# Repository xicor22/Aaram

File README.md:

# Aaram  
PCB design for retro fitting old switch boards with new tech to control it remotely using ESP32-C6-Mini-N1.

## Features
1. Controls 4 loads using
  - 1 Triac 
      > Note: Triac circuit has added protection for the back EMF generated by inductive load like fan.
  - 3 Relays for controlling other resistive loads
      > Try not use heavy inductive load using relays. During testing, the MCU was bugging out when load was switched.
2. Input from switches.
      - To reduce rewiring the whole switch board, directly connect the rocker switch output terminal to the input provided on the board.
      - The FULL BRIDGE RECTIFIER rectifies the AC which is sent to the quad channel opto with a 100k resistor in series for current limiting. The output from the opto is read by the ESP.
3. Fuse holder in series with the AC input for overload protection. 
4. Varistor on all AC output terminals for protection from transient spikes.
5. Added support for IR receiver and transmitter.
6. Uses DHT22 for temperature and humidity sensor.
7. ESPHome Yaml config - [Link](https://github.com/xicor22/Aaram/blob/main/ESPHome_Template.yaml)
## Schematic

## Images
|View|Image|
|----|-----|
|Both Layers| |
|1<sup>st</sup> Layer| |
|2<sup>nd</sup> Layer| |
|3D Top view| |
|3D Bottom view| |

## To-Do
1. ~~Design 3D printables case for the PCB.~~ **Done**
2. Update ESPHOME yaml config.

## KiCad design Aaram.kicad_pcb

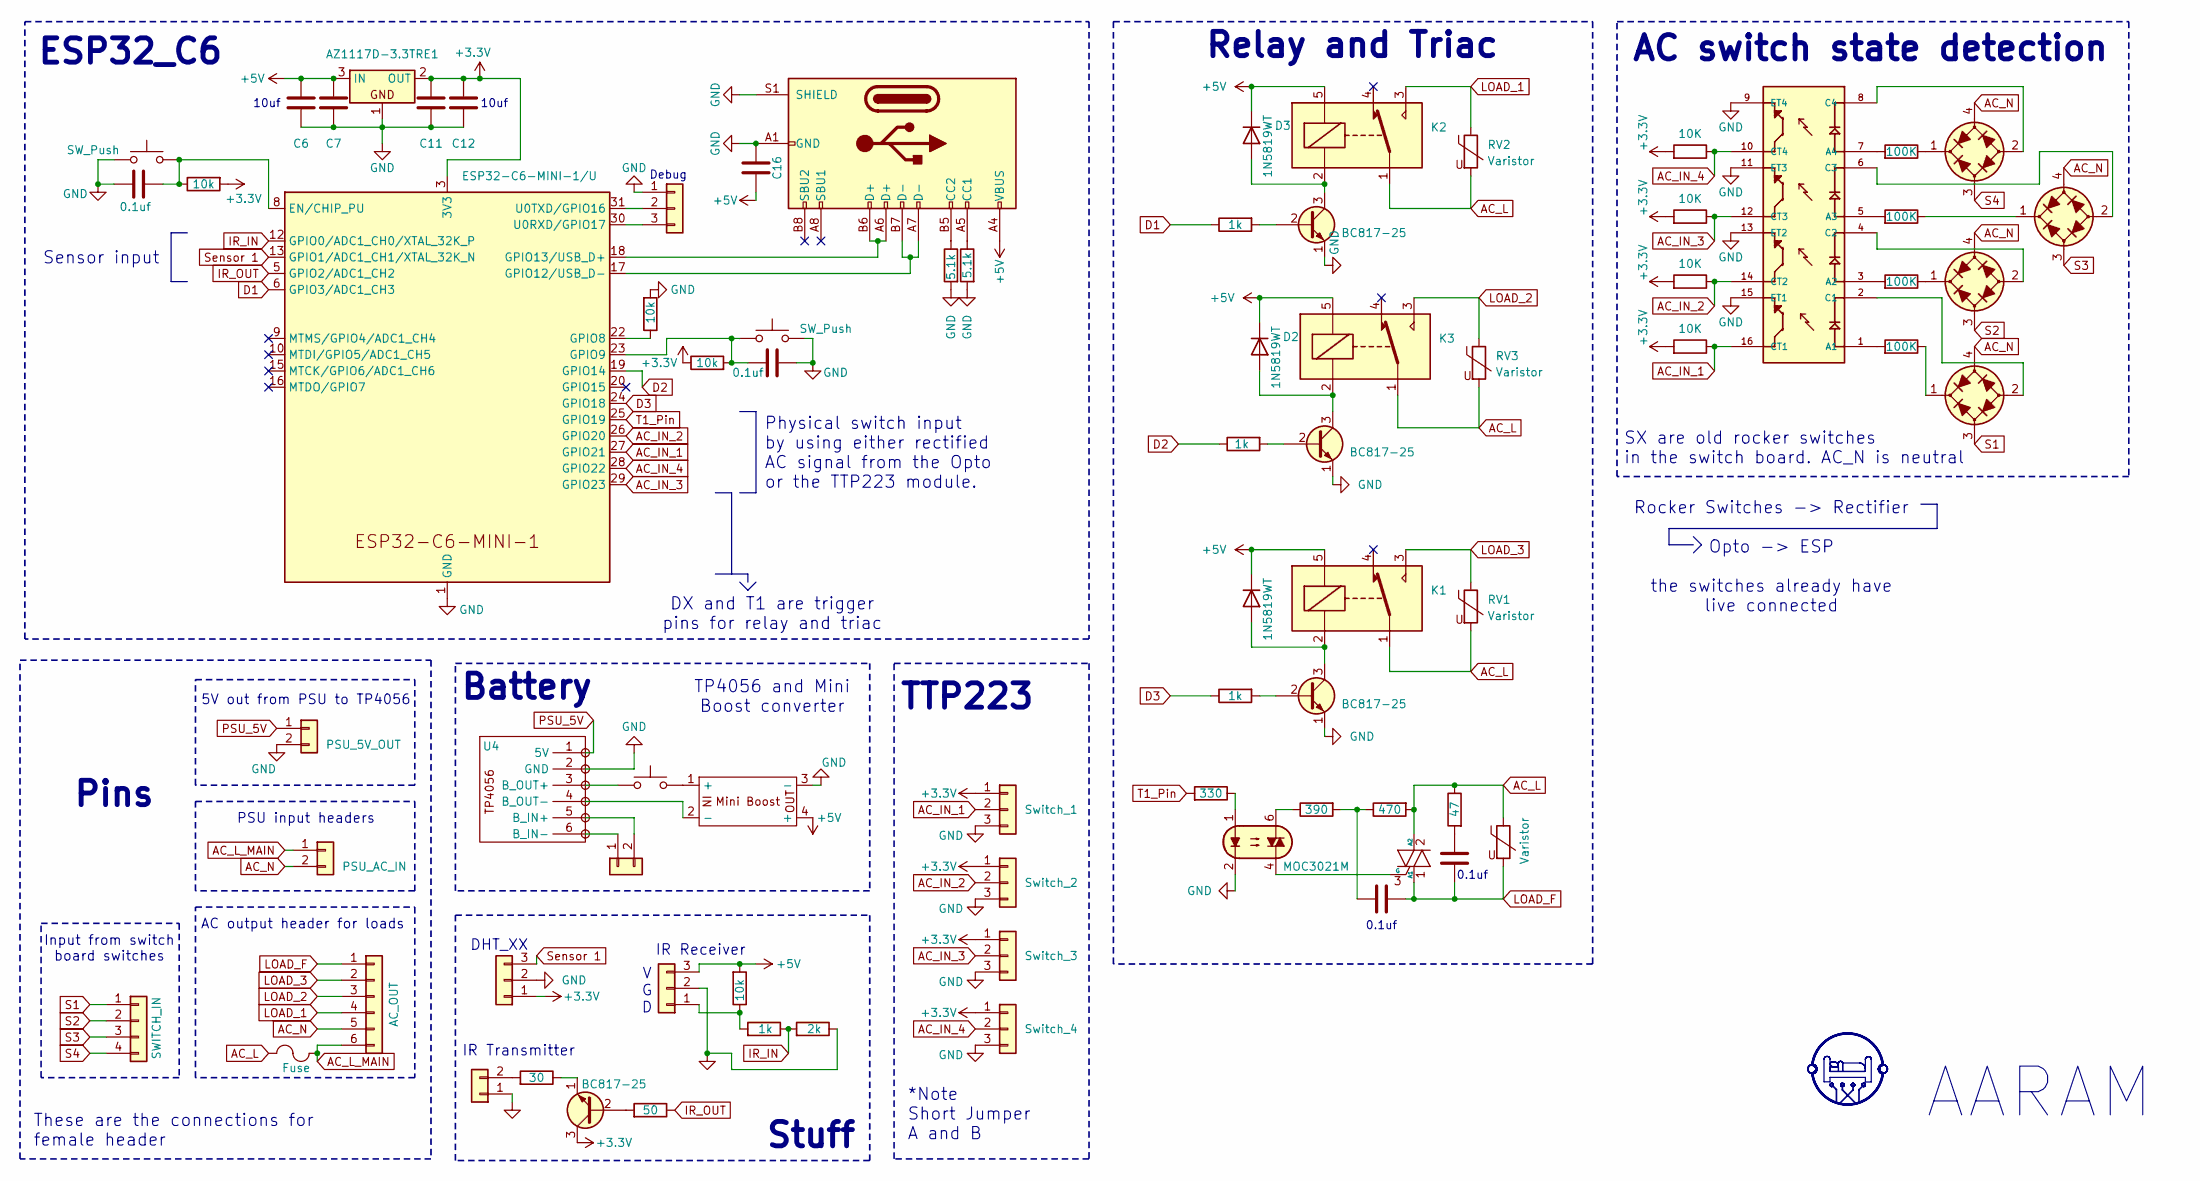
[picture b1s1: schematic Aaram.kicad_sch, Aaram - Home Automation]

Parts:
C1, C4: CP_Axial_L10.0mm_D4.5mm_P15.00mm; Axial_Capacitor_P10mm_W4.5mm
C6, C7, C11, C12: 10uf; C_1206_3216Metric_Pad1.42x1.75mm
C16: 1uf; C_1206_3216Metric_Pad1.42x1.75mm
C18, C19: 0.1uf; C_1206_3216Metric_Pad1.42x1.75mm
D1, D2, D3: 1N5819WT; D_SMA_Handsoldering
D8, D9, D10, D11: MB6S; Diode_Bridge_MBS
F1: Fuse; BLX-A
J1, J10, J11: Conn_01x03; PinSocket_1x03_P2.54mm_Vertical
J2, J9: Conn_01x02; PinSocket_1x02_P2.54mm_Vertical
J3: AC_OUT; 1x06_P5.00mm_D1.50mm
J4: SWITCH_IN; PinSocket_1x04_P2.54mm_Vertical
J5: PSU_5V_OUT; PinSocket_1x02_P2.54mm_Vertical
J6: PSU_AC_IN; PinSocket_1x02_P2.54mm_Vertical
J8: USB_C_Receptacle_USB2.0_16P; USB_C_Receptacle_GCT_USB4105-xx-A_16P_TopMnt_Horizontal
K1, K2, K3: 10A cube relay; Relay_SPDT_SANYOU_SRD_Series_Form_C
OC1: MOC3021M; DIP-6_W7.62mm_LongPads
Q1: BT136-600; TO-220-3_Vertical
Q2, Q3, Q4, Q5: BC817-25; TSOT-23_HandSoldering
R1, R2, R3, R9: 1k; R_1206_3216Metric_Pad1.42x1.75mm_HandSolder
R4: 330; R_1206_3216Metric_Pad1.42x1.75mm_HandSolder
R5: 47; R_2512_6332Metric_Pad1.52x3.35mm_HandSolder
R6: 390; R_2512_6332Metric_Pad1.52x3.35mm_HandSolder
R7: 470; R_2512_6332Metric_Pad1.52x3.35mm_HandSolder
R8: 2k; R_1206_3216Metric_Pad1.42x1.75mm_HandSolder
R10, R16, R21, R22: 10k; R_1206_3216Metric_Pad1.42x1.75mm_HandSolder
R11: 30; R_1206_3216Metric_Pad1.42x1.75mm_HandSolder
R12, R14: 5.1k; R_1206_3216Metric_Pad1.42x1.75mm_HandSolder
R13: 50; R_1206_3216Metric_Pad1.42x1.75mm_HandSolder
R15, R17, R19, R23: 100K; R_2512_6332Metric_Pad1.52x3.35mm_HandSolder
R20, R25, R26, R27: 10K; R_1206_3216Metric_Pad1.42x1.75mm_HandSolder
RV1, RV2, RV3, RV4: Varistor; Varistor_10D431K
SW1, SW4: SW_Push; Tactile switch 6x3
SW2: SW_Push; SMD Tactile switch
Switch_1, Switch_2, Switch_3, Switch_4: Conn_01x03_Socket; JST_SH_BM03B-SRSS-TB_1x03-1MP_P1.00mm_Vertical
U1: ESP32-C6-MINI-1/U; ESP32-C6-MINI-1
U2: AZ1117D-3.3TRE1; TO-252-2
U3: Mini_Boost
U4: TP4056-18650
U5: TLP281-4GB_F_; SOP127P780X200-16N

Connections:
+3.3V: C11.2, C12.2, J1.1, Q5.3 (C), R10.1, R20.1, R21.2, R25.1, R26.1, R27.1, Switch_1.1, Switch_2.1, Switch_3.1, Switch_4.1, U1.3 (3V3), U2.2 (OUT)
+5V: C6.2, C7.2, C16.1, D1.1 (K), D2.1 (K), D3.1 (K), J8.A4 (VBUS), J8.A9 (VBUS), J8.B4 (VBUS), J8.B9 (VBUS), J10.3, K1.5, K2.5, K3.5, R16.1, U2.3 (IN), U3.4 (+)
AC_IN_1: R26.2, Switch_1.2, U1.27 (GPIO21), U5.16 (CT1)
AC_IN_2: R25.2, Switch_2.2, U1.26 (GPIO20), U5.14 (CT2)
AC_IN_3: R20.2, Switch_3.2, U1.29 (GPIO23), U5.12 (CT3)
AC_IN_4: R27.2, Switch_4.2, U1.28 (GPIO22), U5.10 (CT4)
AC_L: F1.1, K1.1, K2.1, K3.1, Q1.2 (A2), R5.2, R7.1, RV1.2, RV2.2, RV3.2, RV4.1
AC_L_MAIN: F1.2, J3.6, J6.1
AC_N: D8.4 (2), D9.4 (2), D10.4 (2), D11.4 (2), J3.5, J6.2
D1: R2.2, U1.6 (GPIO3/ADC1_CH3)
D2: R1.2, U1.19 (GPIO14)
D3: R3.2, U1.24 (GPIO18)
GND: C6.1, C7.1, C11.1, C12.1, C16.2, C18.1, C19.1, J1.2, J2.1, J5.2, J8.A1 (GND), J8.A12 (GND), J8.B1 (GND), J8.B12 (GND), J8.S1 (SHIELD), J10.2, J11.1, OC1.2, Q2.1 (E), Q3.1 (E), Q4.1 (E), R8.2, R12.1, R14.1, R22.1, SW1.1, SW4.1, Switch_1.3, Switch_2.3, Switch_3.3, Switch_4.3, U1.1 (GND), U1.2 (GND), U1.11 (GND), U1.14 (GND), U1.36 (GND), U1.37 (GND), U1.38 (GND), U1.39 (GND), U1.40 (GND), U1.41 (GND), U1.42 (GND), U1.43 (GND), U1.44 (GND), U1.45 (GND), U1.46 (GND), U1.47 (GND), U1.48 (GND), U1.49 (GND), U1.50 (GND), U1.51 (GND), U1.52 (GND), U1.53 (GND), U2.1, U3.3 (-), U4.2 (GND), U5.9 (ET4), U5.11 (ET3), U5.13 (ET2), U5.15 (ET1)
IR_IN: R8.1, R9.2, U1.12 (GPIO0/ADC1_CH0/XTAL_32K_P)
IR_OUT: R13.2, U1.5 (GPIO2/ADC1_CH2)
LOAD_1: J3.4, K2.3, RV2.1
LOAD_2: J3.3, K3.3, RV3.1
LOAD_3: J3.2, K1.3, RV1.1
LOAD_F: C1.2, C4.2, J3.1, Q1.1 (A1), RV4.2
unnamed: C1.1, R6.1, R7.2
unnamed: C4.1, R5.1
unnamed: D1.2 (A), K1.2, Q4.3 (C)
unnamed: D2.2 (A), K3.2, Q2.3 (C)
unnamed: D3.2 (A), K2.2, Q3.3 (C)
unnamed: D8.1 (+), R23.2
unnamed: D8.2 (-), U5.2 (C1)
unnamed: D9.1 (+), R15.2
unnamed: D9.2 (-), U5.4 (C2)
unnamed: D10.1 (+), R17.2
unnamed: D10.2 (-), U5.6 (C3)
unnamed: D11.1 (+), R19.2
unnamed: D11.2 (-), U5.8 (C4)
unnamed: J2.2, R11.1
unnamed: J8.A5 (CC1), R12.2
unnamed: J8.B5 (CC2), R14.2
unnamed: J9.1, U4.6 (B_IN-)
unnamed: J9.2, U4.5 (B_IN+)
unnamed: J10.1, R9.1, R16.2
unnamed: J11.2, U1.31 (U0TXD/GPIO16)
unnamed: J11.3, U1.30 (U0RXD/GPIO17)
unnamed: OC1.1, R4.2
unnamed: OC1.6, R6.2
unnamed: OC1.4, Q1.3 (G)
unnamed: Q2.2 (B), R1.1
unnamed: Q3.2 (B), R2.1
unnamed: Q4.2 (B), R3.1
unnamed: Q5.2 (B), R13.1
unnamed: Q5.1 (E), R11.2
unnamed: SW2.1, U3.1 (+)
unnamed: C18.2, R10.2, SW1.2, U1.8 (EN/CHIP_PU)
unnamed: R22.2, U1.22 (GPIO8)
unnamed: C19.2, R21.1, SW4.2, U1.23 (GPIO9)
unnamed: J8.A7 (D-), J8.B7 (D-), U1.17 (GPIO12/USB_D-)
unnamed: J8.A6 (D+), J8.B6 (D+), U1.18 (GPIO13/USB_D+)
unnamed: SW2.2, U4.3 (B_OUT+)
unnamed: U3.2 (-), U4.4 (B_OUT-)
unnamed: R23.1, U5.1 (A1)
unnamed: R15.1, U5.3 (A2)
unnamed: R17.1, U5.5 (A3)
unnamed: R19.1, U5.7 (A4)
PSU_5V: J5.1, U4.1 (5V)
S1: D8.3 (1), J4.1
S2: D9.3 (1), J4.2
S3: D10.3 (1), J4.3
S4: D11.3 (1), J4.4
Sensor 1: J1.3, U1.13 (GPIO1/ADC1_CH1/XTAL_32K_N)
T1_Pin: R4.1, U1.25 (GPIO19)

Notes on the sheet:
IR Transmitter
0.1uf
Sensor input
Input from switch board switches
Physical switch input by using either rectified AC signal from the Opto or the TTP223 module.
5V out from PSU to TP4056
AC switch state detection
TP4056 and Mini Boost converter
Relay and Triac
10uf
Debug
Pins
TTP223
Rocker Switches -> Rectifier Opto -> ESP the switches already have live connected
V G D
PSU input headers
AARAM
Battery
IR Receiver
ESP32_C6
DHT_XX
Stuff
*Note Short Jumper A and B
These are the connections for female header
AC output header for loads
DX and T1 are trigger pins for relay and triac
SX are old rocker switches in the switch board. AC_N is neutral

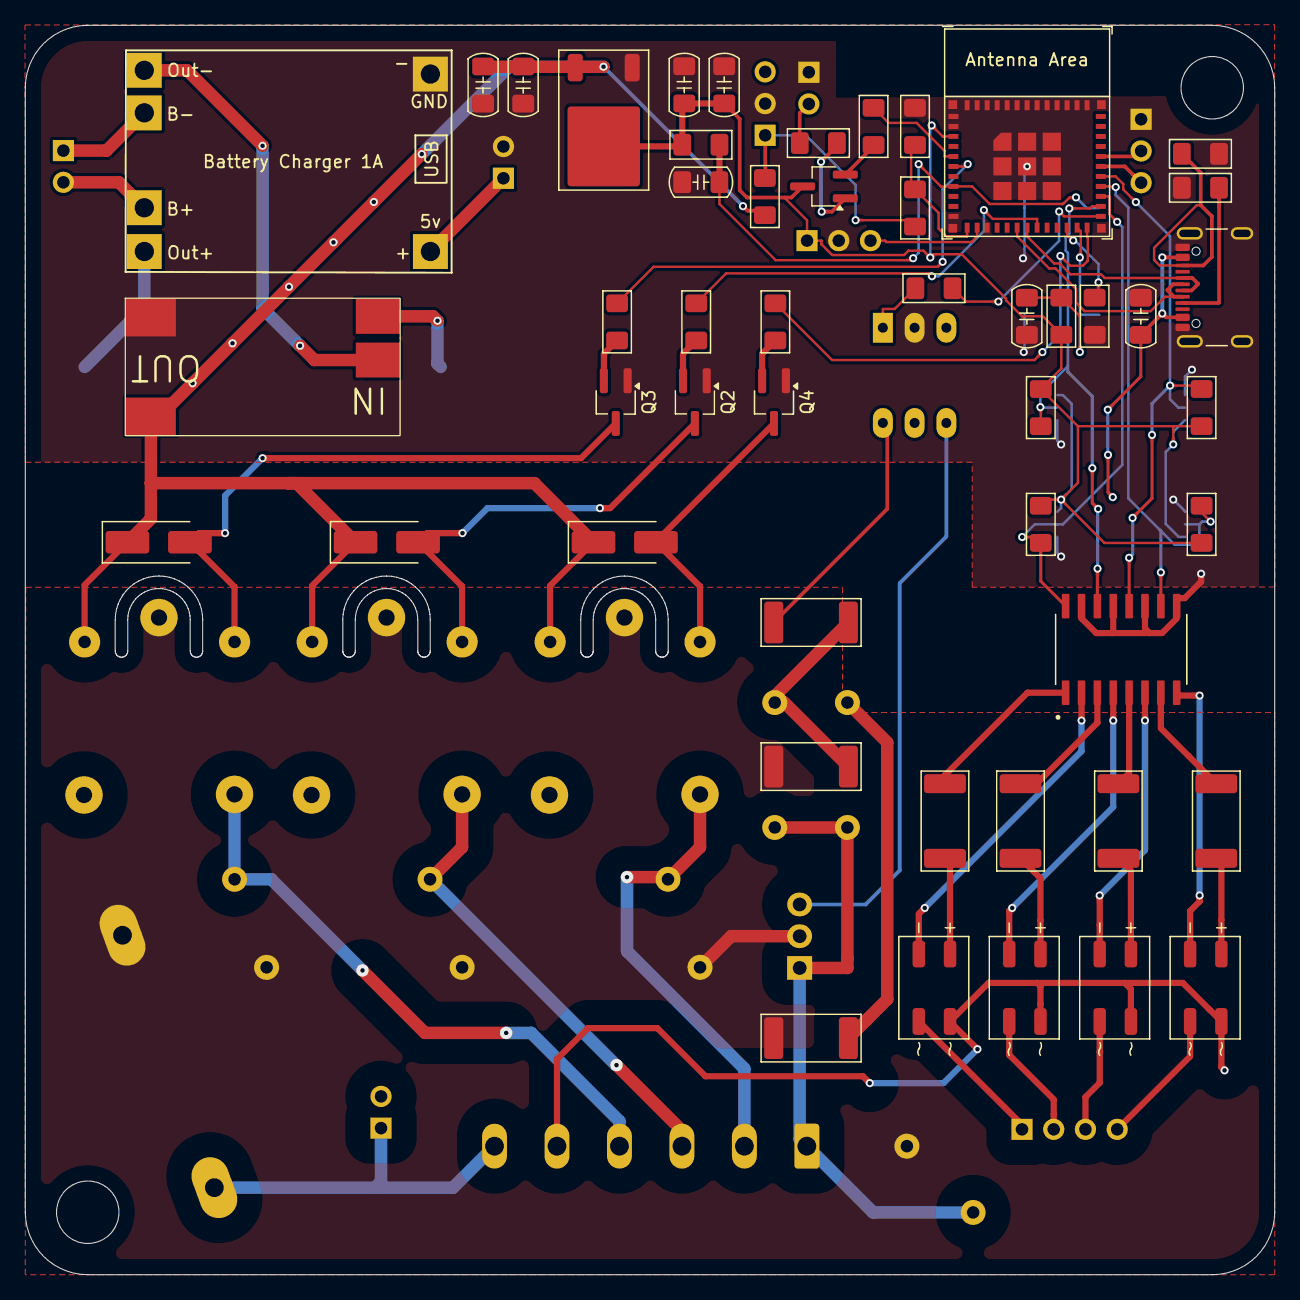
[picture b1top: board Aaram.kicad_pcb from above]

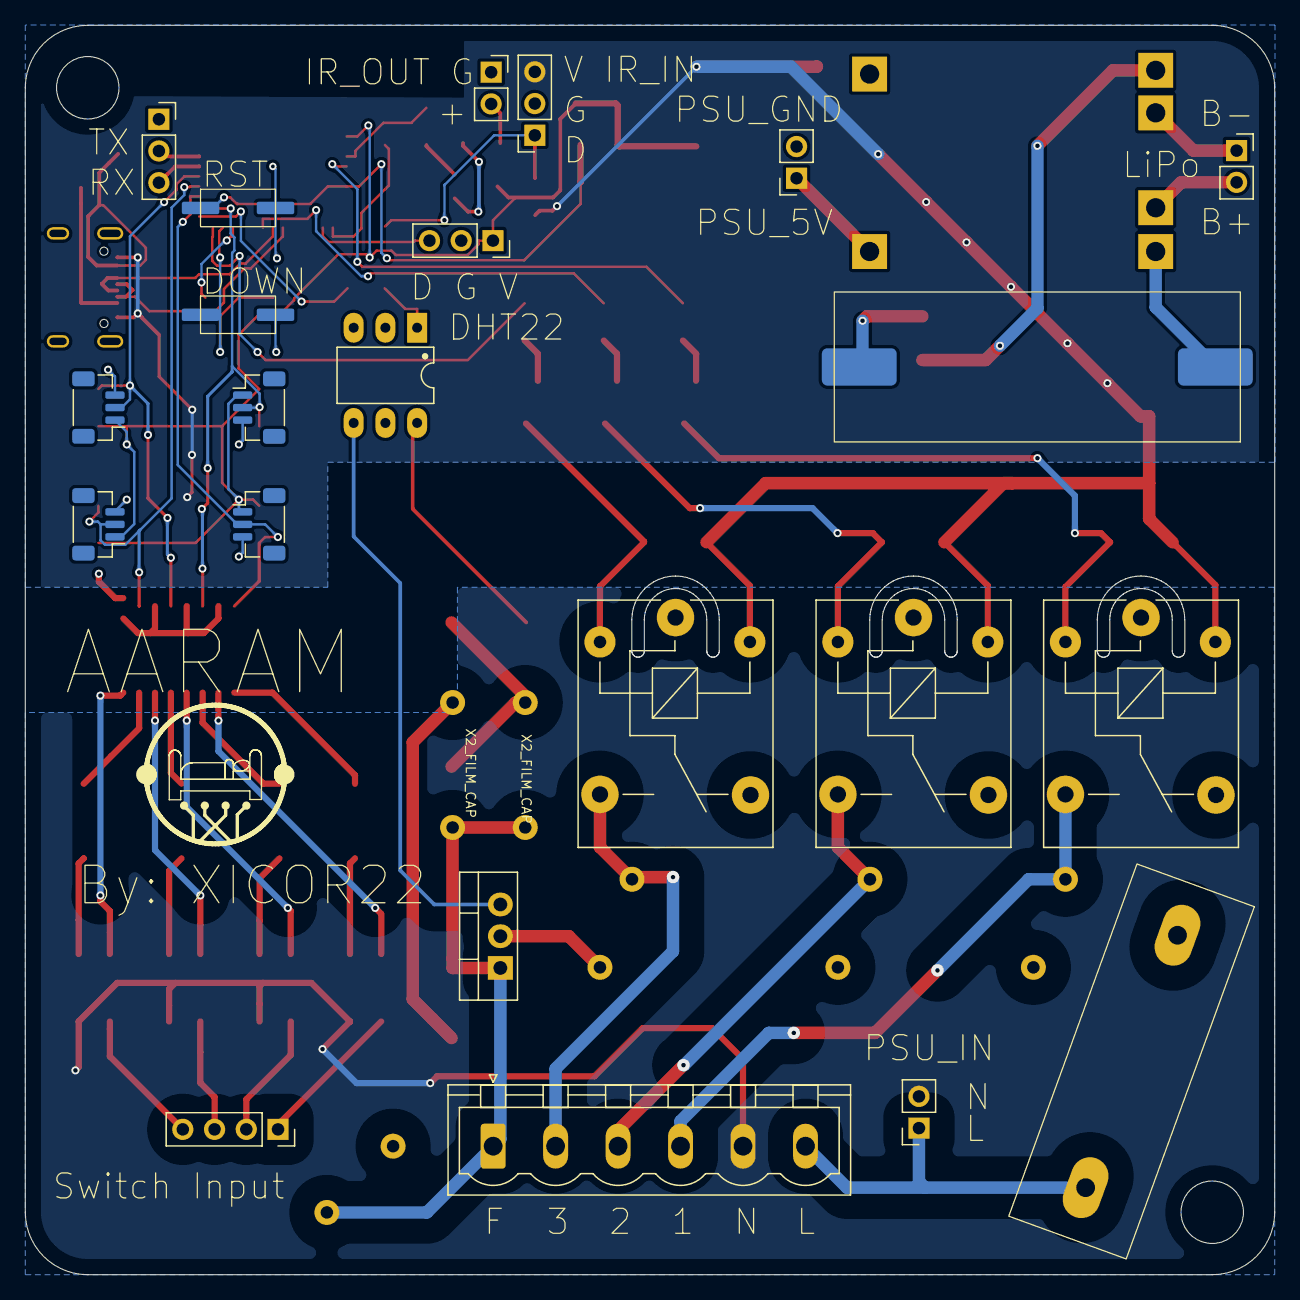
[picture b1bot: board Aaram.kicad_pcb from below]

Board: 2 copper layers, 100.0 x 100.0 mm, 77 parts (28 on the bottom side), 67 nets.

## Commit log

2024-12-19 Added the files
2024-12-19 Added the images
2024-12-19 minor update
2024-12-19 Added schematics
2024-12-20 Added 5v connection to relays
2024-12-20 Updated the images
2024-12-20 Fixed edge cut layer
2024-12-23 Fixed unconnected tracks of triac
2025-01-10 Updated Silkscreen and connections
    Moved the fan control from GPIO4 to GPIO 13, made changes to the silkscreen and redid some of the tracks for better layout.
2025-01-10 Added yaml config and updated the ibom file
    Added yaml config as template for ESPHome
2025-01-14 Component update
    Changed most of the components to use SMD form factor, updated clearance between components in the AC zone and updated the tracks.
2025-01-20 Major Update
    1. Added MOVs for high voltage protection
    2. Added support for zero cross detection
    3. Used SMD components where possible
    4. Better AC detection
2025-01-20 Change footprinnt
    Changed transistor footprint
2025-03-12 Updated mostly everything
2025-03-19 Big Update
2025-04-15 Major Update
    - Removed All 3D related files for now.
    - Updated the Schematics and PCB
    - Updated the assets
2025-04-15 File move
2025-04-15 Major Update (#2)
    * Updated mostly everything
    * Big Update
    * Major Update
    - Removed All 3D related files for now.
    - Updated the Schematics and PCB
    - Updated the assets
2025-04-15 Add png
2025-04-16 3D stuff
    Added PCB step file, Designed a case for the pcb
2025-04-17 Updated enclosure lid
